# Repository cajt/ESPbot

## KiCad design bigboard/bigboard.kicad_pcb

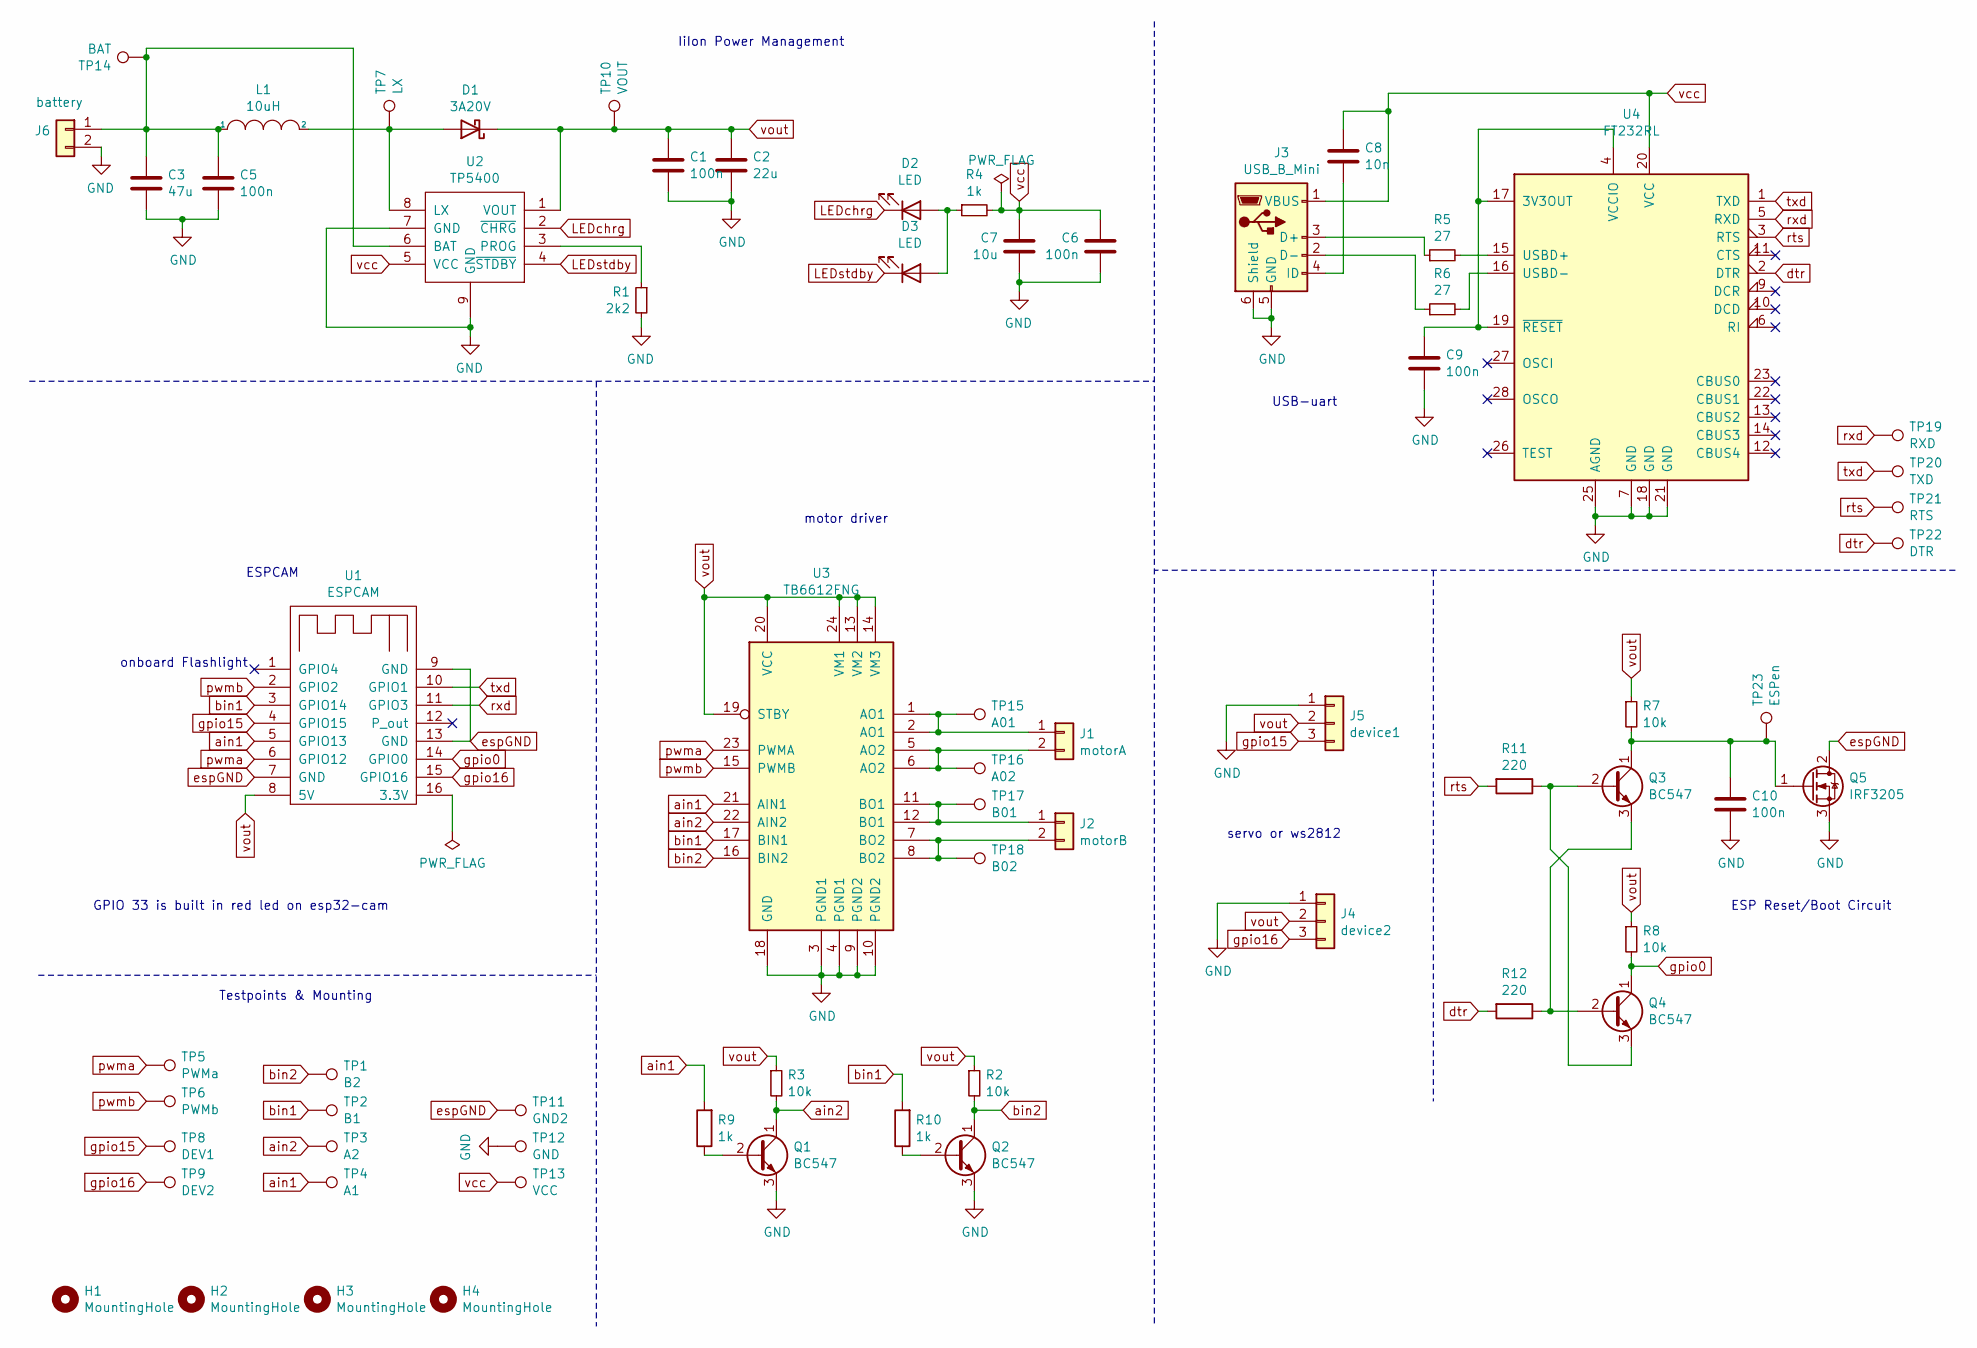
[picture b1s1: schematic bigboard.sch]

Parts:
C1, C5, C6, C9, C10: 100n; C_Disc_D3.0mm_W1.6mm_P2.50mm
C2: 22u; CP_Radial_D10.0mm_P2.50mm_P5.00mm
C3: 47u; CP_Radial_D10.0mm_P2.50mm_P5.00mm
C7: 10u; CP_Radial_D10.0mm_P2.50mm_P5.00mm
C8: 10n; C_Disc_D4.3mm_W1.9mm_P5.00mm
D1: 3A20V; D_A-405_P7.62mm_Horizontal
D2, D3: LED; LED_D3.0mm
H1, H2, H3, H4: MountingHole; MountingHole_3.2mm_M3_DIN965_Pad
J1: motorA; PinHeader_1x02_P2.54mm_Vertical
J2: motorB; PinHeader_1x02_P2.54mm_Vertical
J3: USB_B_Mini; USB_Micro-B_Molex-105017-0001
J4: device2; PinHeader_1x03_P2.54mm_Vertical
J5: device1; PinHeader_1x03_P2.54mm_Vertical
J6: battery; PinHeader_1x02_P2.54mm_Vertical
L1: 10uH; L_Toroid_Vertical_L10.0mm_W5.0mm_P5.08mm
Q1, Q2, Q3, Q4: BC547; TO-92_Inline
Q5: IRF3205; TO-220F-3_Horizontal_TabDown
R1: 2k2; R_Axial_DIN0204_L3.6mm_D1.6mm_P5.08mm_Horizontal
R2, R3, R7, R8: 10k; R_Axial_DIN0204_L3.6mm_D1.6mm_P5.08mm_Horizontal
R4, R9, R10: 1k; R_Axial_DIN0204_L3.6mm_D1.6mm_P5.08mm_Horizontal
R5, R6: 27; R_Axial_DIN0204_L3.6mm_D1.6mm_P5.08mm_Horizontal
R11, R12: 220; R_Axial_DIN0204_L3.6mm_D1.6mm_P5.08mm_Horizontal
TP1: B2; TestPoint_Bridge_Pitch2.54mm_Drill0.7mm
TP2: B1; TestPoint_Bridge_Pitch2.54mm_Drill0.7mm
TP3: A2; TestPoint_Bridge_Pitch2.54mm_Drill0.7mm
TP4: A1; TestPoint_Bridge_Pitch2.54mm_Drill0.7mm
TP5: PWMa; TestPoint_Bridge_Pitch2.54mm_Drill0.7mm
TP6: PWMb; TestPoint_Bridge_Pitch2.54mm_Drill0.7mm
TP7: LX; TestPoint_Bridge_Pitch2.54mm_Drill0.7mm
TP8: DEV1; TestPoint_Bridge_Pitch2.54mm_Drill0.7mm
TP9: DEV2; TestPoint_Bridge_Pitch2.54mm_Drill0.7mm
TP10: VOUT; TestPoint_Bridge_Pitch2.54mm_Drill0.7mm
TP11: GND2; TestPoint_Bridge_Pitch2.54mm_Drill0.7mm
TP12: GND; TestPoint_Bridge_Pitch2.54mm_Drill0.7mm
TP13: VCC; TestPoint_Bridge_Pitch2.54mm_Drill0.7mm
TP14: BAT; TestPoint_Bridge_Pitch2.54mm_Drill0.7mm
TP15: A01; TestPoint_Bridge_Pitch2.54mm_Drill0.7mm
TP16: A02; TestPoint_Bridge_Pitch2.54mm_Drill0.7mm
TP17: B01; TestPoint_Bridge_Pitch2.54mm_Drill0.7mm
TP18: B02; TestPoint_Bridge_Pitch2.54mm_Drill0.7mm
TP19: RXD; TestPoint_Bridge_Pitch2.54mm_Drill0.7mm
TP20: TXD; TestPoint_Bridge_Pitch2.54mm_Drill0.7mm
TP21: RTS; TestPoint_Bridge_Pitch2.54mm_Drill0.7mm
TP22: DTR; TestPoint_Bridge_Pitch2.54mm_Drill0.7mm
TP23: ESPen; TestPoint_Bridge_Pitch2.54mm_Drill0.7mm
U1: ESPCAM; ESPCAM_bottom
U2: TP5400; ESOP8-F.Cu-only
U3: TB6612FNG; SSOP-24_5.3x8.2mm_P0.65mm
U4: FT232RL; SSOP-28_5.3x10.2mm_P0.65mm

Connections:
ESPen: C10.1, Q3.1 (C), Q5.1 (G), R7.2, TP23.1
GND: C1.2, C2.2, C3.2, C5.2, C6.2, C7.2, C9.2, C10.2, J3.5 (GND), J3.6 (Shield), J4.1, J5.1, J6.2, Q1.3 (E), Q2.3 (E), Q5.3 (S), R1.2, TP12.1, U2.7 (GND), U2.9 (GND), U3.3 (PGND1), U3.4 (PGND1), U3.9 (PGND2), U3.10 (PGND2), U3.18 (GND), U4.7 (GND), U4.18 (GND), U4.21 (GND), U4.25 (AGND)
LEDchrg: D2.1 (K), U2.2 (~CHRG)
LEDstdby: D3.1 (K), U2.4 (~STDBY)
unnamed: C8.2, J3.4 (ID)
unnamed: C9.1, U4.4 (VCCIO), U4.17 (3V3OUT), U4.19 (~RESET~)
unnamed: D1.2 (A), L1.2, TP7.1, U2.8 (LX)
unnamed: D2.2 (A), D3.2 (A), R4.1
unnamed: J1.1, TP15.1, U3.1 (AO1), U3.2 (AO1)
unnamed: J1.2, TP16.1, U3.5 (AO2), U3.6 (AO2)
unnamed: J2.1, TP17.1, U3.11 (BO1), U3.12 (BO1)
unnamed: J2.2, TP18.1, U3.7 (BO2), U3.8 (BO2)
unnamed: J3.2 (D-), R6.1
unnamed: J3.3 (D+), R5.1
unnamed: Q1.2 (B), R9.1
unnamed: Q2.2 (B), R10.1
unnamed: Q3.2 (B), Q4.3 (E), R11.1
unnamed: Q3.3 (E), Q4.2 (B), R12.1
unnamed: R1.1, U2.3 (PROG)
unnamed: R5.2, U4.15 (USBD+)
unnamed: R6.2, U4.16 (USBD-)
ain1: R9.2, TP4.1, U1.5 (GPIO13), U3.21 (AIN1)
ain2: Q1.1 (C), R3.2, TP3.1, U3.22 (AIN2)
bat: C3.1, C5.1, J6.1, L1.1, TP14.1, U2.6 (BAT)
bin1: R10.2, TP2.1, U1.3 (GPIO14), U3.17 (BIN1)
bin2: Q2.1 (C), R2.2, TP1.1, U3.16 (BIN2)
dtr: R12.2, TP22.1, U4.2 (DTR)
espGND: Q5.2 (D), TP11.1, U1.7 (GND), U1.9 (GND), U1.13 (GND)
gpio0: Q4.1 (C), R8.2, U1.14 (GPIO0)
gpio15: J5.3, TP8.1, U1.4 (GPIO15)
gpio16: J4.3, TP9.1, U1.15 (GPIO16)
pwma: TP5.1, U1.6 (GPIO12), U3.23 (PWMA)
pwmb: TP6.1, U1.2 (GPIO2), U3.15 (PWMB)
rts: R11.2, TP21.1, U4.3 (RTS)
rxd: TP19.1, U1.11 (GPIO3), U4.5 (RXD)
txd: TP20.1, U1.10 (GPIO1), U4.1 (TXD)
vcc: C6.1, C7.1, C8.1, J3.1 (VBUS), R4.2, TP13.1, U2.5 (VCC), U4.20 (VCC)
vout: C1.1, C2.1, D1.1 (K), J4.2, J5.2, R2.1, R3.1, R7.1, R8.1, TP10.1, U1.8 (5V), U2.1 (VOUT), U3.13 (VM2), U3.14 (VM3), U3.19 (STBY), U3.20 (VCC), U3.24 (VM1)

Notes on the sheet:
IiIon Power Management
USB-uart
motor driver
ESPCAM
ESP Reset/Boot Circuit
onboard Flashlight
servo or ws2812
GPIO 33 is built in red led on esp32-cam
Testpoints & Mounting

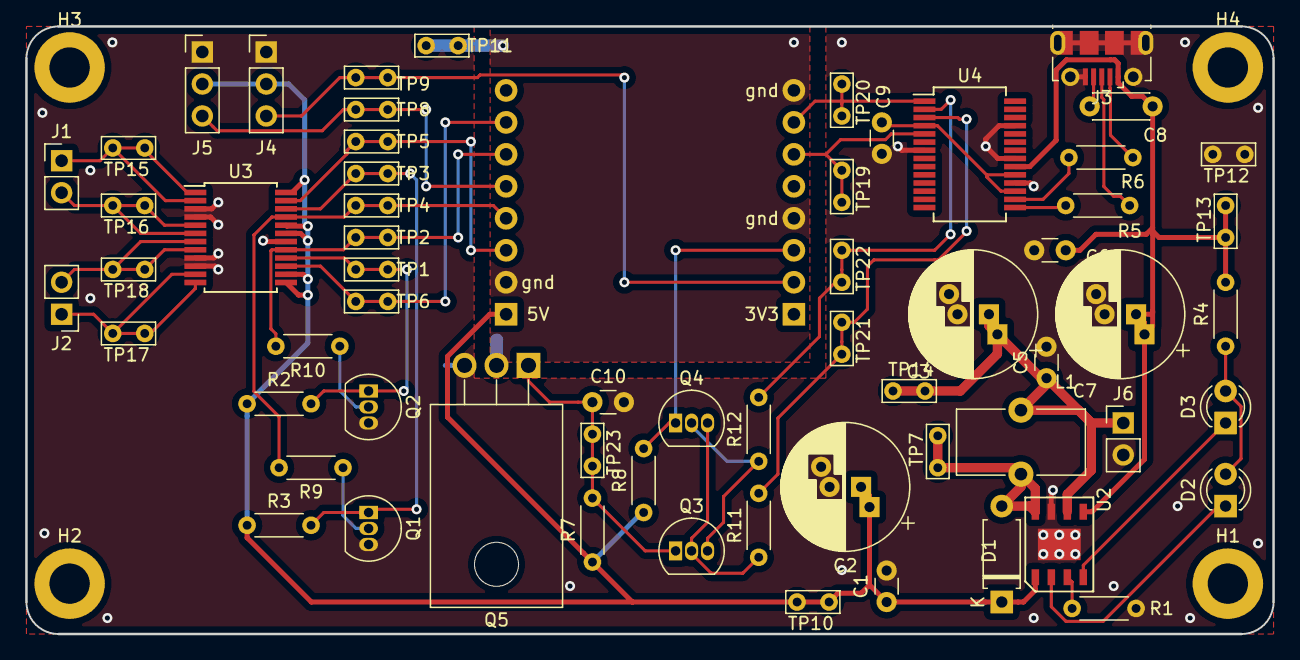
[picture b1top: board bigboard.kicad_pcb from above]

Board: 2 copper layers, 99.1 x 48.3 mm, 67 parts (0 on the bottom side), 38 nets.

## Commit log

2021-01-24 minor stylistic suggestions & path fixes
2021-01-24 schematic output for easier viewing
